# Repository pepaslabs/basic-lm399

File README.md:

# basic-lm399
A very basic LM399 voltage reference board design.

See the notes about the [latest release](kicad/releases/v1/README.md).

See also [svenskelektronik's fork](https://github.com/svenskelektronik/basic-lm399), which updates this project for the modern releases of KiCAD.

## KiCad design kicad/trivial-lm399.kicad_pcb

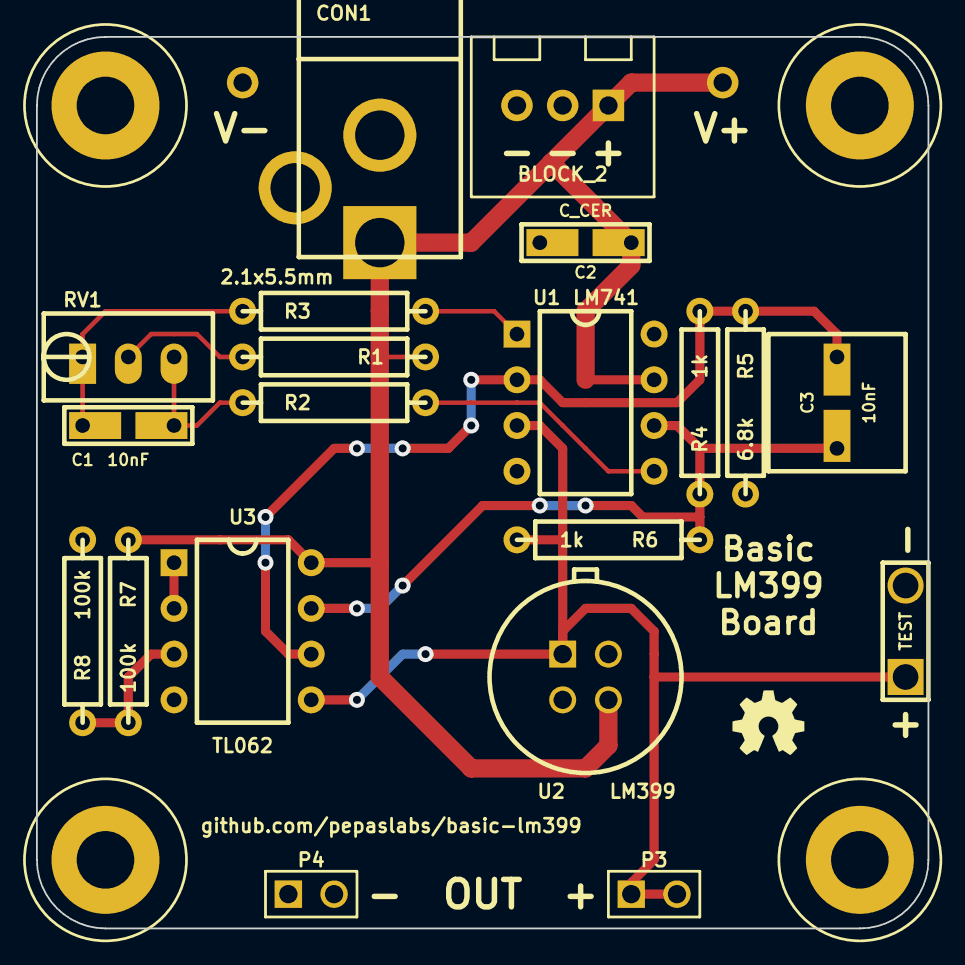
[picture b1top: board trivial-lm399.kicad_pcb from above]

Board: 2 copper layers, 49.5 x 49.5 mm, 26 parts (0 on the bottom side), 12 nets.

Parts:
BLOCK_2: Val**; TERMINAL_BLOCK_2_5mm
C1: 10nF; CERCAP_2_059B_0805
C2: C_CER; CERCAP_2_059B_0805
C3: 10nF; ANYSSCAP_2_059B_0805
CON1: BARREL_JACK; BARREL_JACK_21x55
H***: Val**; hole_M3
H***#2, H***#3, H***#4: Val**; hole_M3
P1, P2: CONN_1; 1pin_040_069
P3, P4: CONN_2; PIN_ARRAY_2X1
R1, R2, R3: ?; R_AXIAL_0W25_059A_PL
R4, R6: 1k; R_AXIAL_0W25_059A_PL
R5: 6.8k; R_AXIAL_0W25_059A_PL
R7, R8: 100k; R_AXIAL_0W25_059A_PL
RV1: ?; 3296W_PL
TEST: CONN_2; TEST_2
U1: LM741; DIP8_059A_PL
U2: LM399; TO-46-PLASTIC
U3: TL062; DIP8_059A_PL

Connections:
GND: BLOCK_2.2, C2.2, CON1.2, CON1.3, P2.1, P4.1, P4.2, R5.2, R8.2, TEST.2, U1.4, U2.2, U2.4, U3.4
unnamed: R1.2, RV1.2
unnamed: U3.1, U3.2
unnamed: R7.2, R8.1, U3.3
unnamed: C1.1, R2.1, RV1.3
unnamed: C1.2, R3.1, RV1.1
OP+: P3.1, P3.2, R6.2, TEST.1, U1.3, U2.1, U3.5
OP-: C3.2, R4.2, R5.1, U1.2, U3.6
OP_OUT: C3.1, R4.1, R6.1, U1.6, U3.7
TRIM1: R3.2, U1.1
TRIM2: R2.2, U1.5
V+: BLOCK_2.1, C2.1, CON1.1, P1.1, R1.1, R7.1, U1.7, U2.3, U3.8

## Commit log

2018-03-23 initial release
2018-03-23 rolling back to version which matches boards
2018-03-23 media
2018-03-23 schematic pngs
2018-03-23 pics
2018-03-23 board renders
2018-03-28 Adding symbols,footprints and 3d_models
    Connector symbols missing, 3d parts missing. Adding symbols,footprints and 3d_models locally to project folders.
2018-03-28 cleaning up
